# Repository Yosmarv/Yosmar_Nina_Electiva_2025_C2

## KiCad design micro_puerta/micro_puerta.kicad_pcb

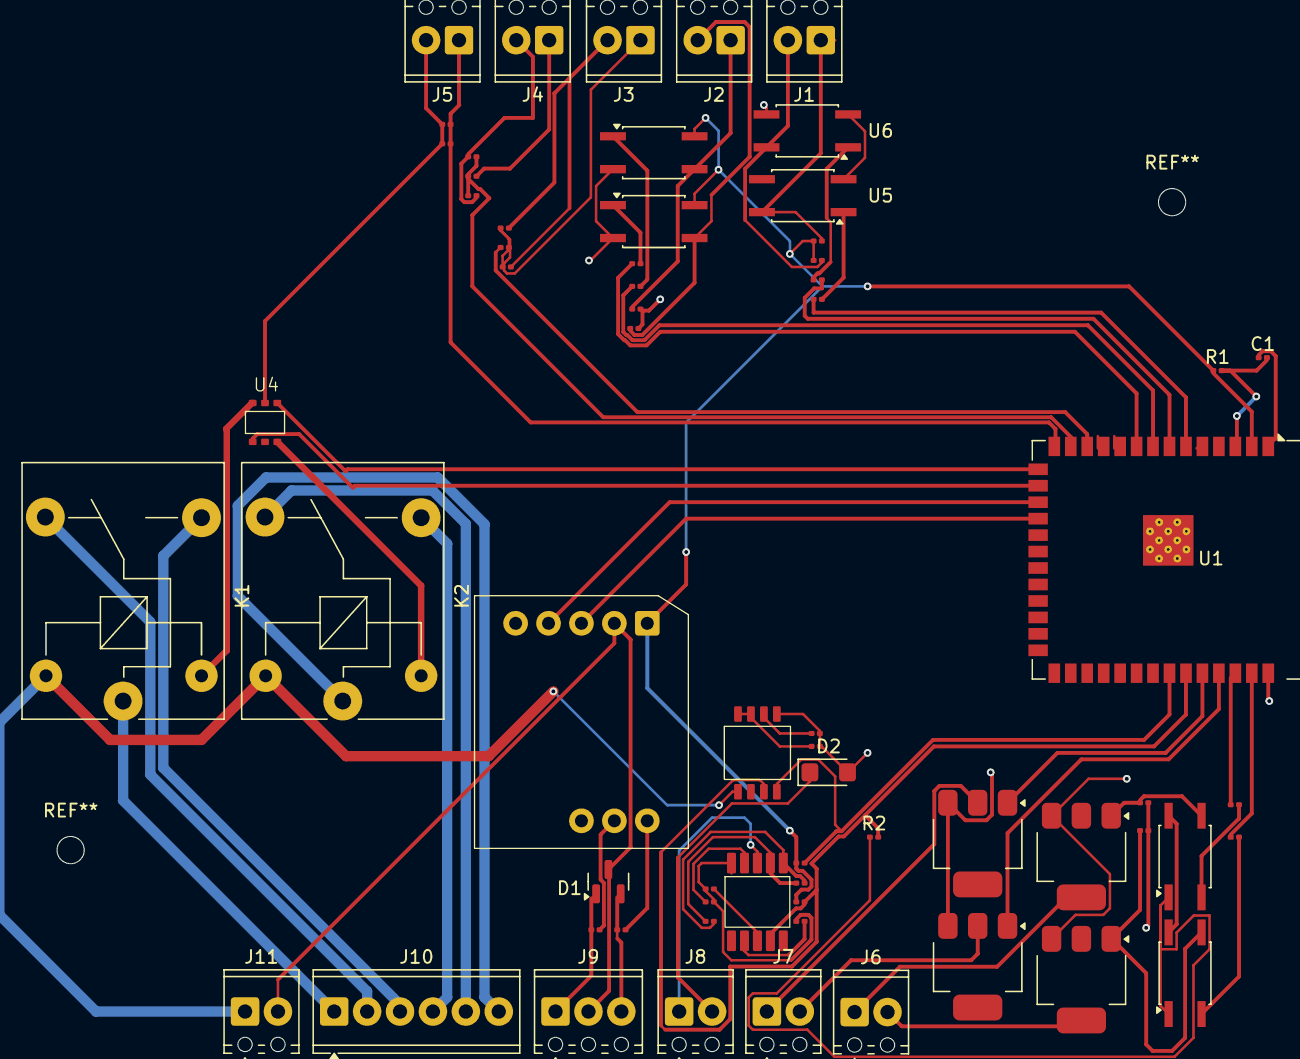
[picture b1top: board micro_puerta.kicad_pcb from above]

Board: 2 copper layers, 64 parts (0 on the bottom side), 59 nets.

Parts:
C1: 10uF; C_0201_0603Metric
C7, C8, C9, C10: 100nF; C_0201_0603Metric
C11: 1uF; C_0201_0603Metric
C12: 220pF; C_0201_0603Metric
D1: SM712_SOT23; SOT-23
D2: SMF24A; D_SMF
J1: Entrada NPN; TerminalBlock_Phoenix_MPT-0,5-2-2.54_1x02_P2.54mm_Horizontal
J2: Entradas PNP; TerminalBlock_Phoenix_MPT-0,5-2-2.54_1x02_P2.54mm_Horizontal
J3: Entrada An 0-32V; TerminalBlock_Phoenix_MPT-0,5-2-2.54_1x02_P2.54mm_Horizontal
J4: Entrada An 0-10V; TerminalBlock_Phoenix_MPT-0,5-2-2.54_1x02_P2.54mm_Horizontal
J5: Entrada An 5-20mA; TerminalBlock_Phoenix_MPT-0,5-2-2.54_1x02_P2.54mm_Horizontal
J6: PNP OUTPUT; TerminalBlock_Phoenix_MPT-0,5-2-2.54_1x02_P2.54mm_Horizontal
J7: NPN OUTPUT; TerminalBlock_Phoenix_MPT-0,5-2-2.54_1x02_P2.54mm_Horizontal
J8: Salidas An; TerminalBlock_Phoenix_MPT-0,5-2-2.54_1x02_P2.54mm_Horizontal
J9: RS485; TerminalBlock_Phoenix_MPT-0,5-3-2.54_1x03_P2.54mm_Horizontal
J10: Relay; TerminalBlock_Phoenix_MPT-0,5-6-2.54_1x06_P2.54mm_Horizontal
J11: Screw_Terminal_01x02; TerminalBlock_Phoenix_MPT-0,5-2-2.54_1x02_P2.54mm_Horizontal
K1, K2: SANYOU_SRD_Form_C; Relay_SPDT_SANYOU_SRD_Series_Form_C
Q1, Q2, Q3, Q4: NCV8402xST; SOT-223
R1: R; R_0201_0603Metric
R2: 2.2K; R_0201_0603Metric
R5, R6, R7: 120; R_0201_0603Metric
R8, R10, R16, R18: 910; R_0201_0603Metric
R9, R11, R17, R19: 412; R_0201_0603Metric
R12, R14: 100; R_0201_0603Metric
R13, R15: 1k; R_0201_0603Metric
R20: 160K; R_0201_0603Metric
R21: 13K; R_0201_0603Metric
R22: 51K; R_0201_0603Metric
R23: 16K; R_0201_0603Metric
R24, R26: 4.7K; R_0201_0603Metric
R25, R27, R28: 10K; R_0201_0603Metric
R29: 2.5K; R_0201_0603Metric
U1: ESP32-S3-WROOM-1
U3: RSM3485ECHT
U4: LK1802
U5, U6, U7, U8, U9, U10: LTV-357T; SO-4_4.4x3.6mm_P2.54mm
U11: GP8201S
U12: GP8303

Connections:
+3.3V: R1.1, R2.1, R9.1, R11.1, R24.1, R26.2, U1.2 (3V3), U3.1 (VCC), U7.1, U8.1, U9.4, U10.4
/board_zorion/A_An_OUT: J8.1, U12.8 (IOUT)
/board_zorion/A_IN_10V: J4.1, R22.1
/board_zorion/A_IN_10V/10V_A_IN_OUT: C9.1, R22.2, R23.1, U1.13 (GPIO19/U1RTS/ADC2_CH8/CLK_OUT2/USB_D-)
/board_zorion/A_IN_32V: C8.1, J3.1, R20.2, R21.1
/board_zorion/A_IN_32V/32V_A_IN_IN: R20.1, U1.12 (GPIO8/TOUCH8/ADC1_CH7/SUBSPICS1)
/board_zorion/A_IN_420mA: C7.1, J5.1, R7.1, U1.14 (GPIO20/U1CTS/ADC2_CH9/CLK_OUT1/USB_D+)
/board_zorion/Ma_OUT/SDA: R2.2, R24.2, U1.35 (MTMS/GPIO42), U11.2 (SDA), U12.2 (SDA)
/board_zorion/Ma_OUT/SLCLK: R26.1, U1.34 (MTDI/GPIO41/CLK_OUT1), U11.1 (SCLK), U12.1 (SLCLK)
/board_zorion/NPN_IN/NPN_IN_IN_1: R8.1, U1.6 (GPIO6/TOUCH6/ADC1_CH5)
/board_zorion/NPN_IN/NPN_IN_IN_2: R10.2, U1.7 (GPIO7/TOUCH7/ADC1_CH6)
/board_zorion/NPN_IN_1: J1.1, R9.2, U5.4
/board_zorion/NPN_IN_2: J1.2, R11.2, U6.4
/board_zorion/NPN_OUT/NPN_OUT_IN_1: Q1.1 (G), U1.36 (U0RXD/GPIO44/CLK_OUT2)
/board_zorion/NPN_OUT/NPN_OUT_IN_2: Q2.1 (G), U1.37 (U0TXD/GPIO43/CLK_OUT1)
/board_zorion/NPN_OUT_1: J7.1, Q1.2 (D), Q1.4 (D)
/board_zorion/NPN_OUT_2: J7.2, Q2.2 (D), Q2.4 (D)
/board_zorion/PNP_IN/PNP_IN_IN_1: R16.1, U1.8 (GPIO15/U0RTS/ADC2_CH4/XTAL_32K_P)
/board_zorion/PNP_IN/PNP_IN_IN_2: R18.1, U1.9 (GPIO16/U0CTS/ADC2_CH5/XTAL_32K_N)
/board_zorion/PNP_IN_1: J2.1, R17.1, U9.3
/board_zorion/PNP_IN_2: J2.2, R19.1, U10.3
/board_zorion/PNP_OUT/PNP_OUT_IN_1: R12.1, U1.38 (GPIO2/TOUCH2/ADC1_CH1)
/board_zorion/PNP_OUT/PNP_OUT_IN_2: R14.1, U1.39 (GPIO1/TOUCH1/ADC1_CH0)
/board_zorion/PNP_OUT_1: J6.1, Q3.2 (D), Q3.4 (D)
/board_zorion/PNP_OUT_2: J6.2, Q4.2 (D), Q4.4 (D)
/board_zorion/RLY1_C: J10.1, K1.1
/board_zorion/RLY1_NC: J10.2, K1.4
/board_zorion/RLY1_NO: J10.3, K1.3
/board_zorion/RLY2_C: J10.4, K2.3
/board_zorion/RLY2_NC: J10.5, K2.4
/board_zorion/RLY2_NO: J10.6, K2.1
/board_zorion/RS485_A: D1.2 (A2), J9.3, R5.2
/board_zorion/RS485_B: D1.1 (A1), J9.1, R6.2
/board_zorion/RS485_driver/RS485_IN: U1.17 (GPIO9/TOUCH9/ADC1_CH8/FSPIHD/SUBSPIHD), U3.4 (RXD)
/board_zorion/RS485_driver/RS485_OUT: U1.18 (GPIO10/TOUCH10/ADC1_CH9/FSPICS0/FSPIIO4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), U3.3 (TXD)
/board_zorion/Rele_IN/RELAY1_IN: U1.15 (GPIO3/TOUCH3/ADC1_CH2), U4.3 (1B)
/board_zorion/Rele_IN/RELAY2_IN: U1.16 (GPIO46), U4.6 (2B)
/board_zorion/V_AN_Out/SEL: C11.1, U11.7 (SEL), U11.8 (V5V)
/board_zorion/V_An_OUT: C10.2, D2.1 (A1), J8.2, U11.6 (VOUT)
GND: C1.1, C7.2, C8.2, C9.2, C10.1, C11.2, C12.2, D1.3 (common), D2.2 (A2), J3.2, J4.2, J5.2, J9.2, J11.2, Q1.3 (S), Q2.3 (S), Q3.3 (S), Q4.3 (S), R7.2, R13.2, R15.2, R17.2, R19.2, R21.2, R23.2, R29.2, U1.1 (GND), U1.40 (GND), U1.41 (GND), U3.2 (GND), U4.2 (E), U5.2, U5.3, U6.2, U6.3, U9.2, U10.2, U11.5 (GND), U12.6 (GND)
unnamed: Q3.1 (G), R13.1, U7.3
unnamed: Q4.1 (G), R15.1, U8.3
unnamed: R8.2, U5.1
unnamed: R10.1, U6.1
unnamed: R12.2, U7.2
unnamed: R14.2, U8.2
unnamed: R16.2, U9.1
unnamed: R18.2, U10.1
unnamed: C1.2, R1.2, U1.3 (EN)
unnamed: R6.1, U3.7 (A)
unnamed: R5.1, U3.6 (B)
unnamed: K1.2, U4.1 (1C)
unnamed: K2.2, U4.4 (2C)
unnamed: R27.2, U12.3 (A0)
unnamed: R25.2, U12.4 (A1)
unnamed: R28.1, U12.9 (A2)
unnamed: C12.1, R29.1, U12.7 (SET)
unnamed: R25.1, R27.1, R28.2, U12.10 (V5V)
VCC: J11.1, K1.5, K2.5, U4.5 (COM), U7.4, U8.4, U11.4 (VCC)

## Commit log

2025-05-23 Tarea Requisitos
2025-05-30 dibujos de FreeCAD
2025-05-30 tarea_solidedge
2025-06-10 parte baja del solid edge
2025-06-13 Diseño de PCB
2025-06-13 garabato
2025-06-14 Diagramas Electricos
2025-06-14 Actualizacion PCB
2025-07-01 Archivo esqematico y FP del modulo
2025-07-14 Actualizacion
2025-07-15 actulizacion 2
2025-07-16 Actualizacion 3
2025-08-08 actualizacion placa
2025-08-08 nueva actualizacion
2025-08-13 Create README.md
    Este es el README del proyecto de la materia de Electiva Mecatronica
2025-08-13 Actualizacion 4 de proyecto
2025-08-14 Actualizacion 5
2025-08-14 Actualizacion 6
2025-08-14 Actualizacion 7
